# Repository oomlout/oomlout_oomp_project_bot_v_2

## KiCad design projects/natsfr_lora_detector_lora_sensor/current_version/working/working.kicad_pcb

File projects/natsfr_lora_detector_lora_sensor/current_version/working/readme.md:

# lora_detector
 
## summary 
* id: natsfr_lora_detector_lora_sensor
* user: natsfr
* name: lora_detector
* board: lora_sensor
* repo: https://github.com/natsfr/Lora_detector
* src_file_repo_kicad_pcb: sensor_board/lora_sensor/lora_sensor.kicad_pcb
* src_file_repo_kicad_pcb_link: https://github.com/natsfr/Lora_detector/tree/master/sensor_board/lora_sensor/lora_sensor.kicad_pcb
* src_file_repo_kicad_sch: sensor_board/lora_sensor/lora_sensor.kicad_sch
* src_file_repo_kicad_sch_link: https://github.com/natsfr/Lora_detector/tree/master/sensor_board/lora_sensor/lora_sensor.kicad_sch

* src_file_repo_sch: 
* src_file_repo_sch_link: https://github.com/natsfr/Lora_detector/tree/master/
* full details link: https://github.com/oomlout/oomlout_oomp_project_bot_v_2/tree/main/projects/natsfr_lora_detector_lora_sensor/current_version/working

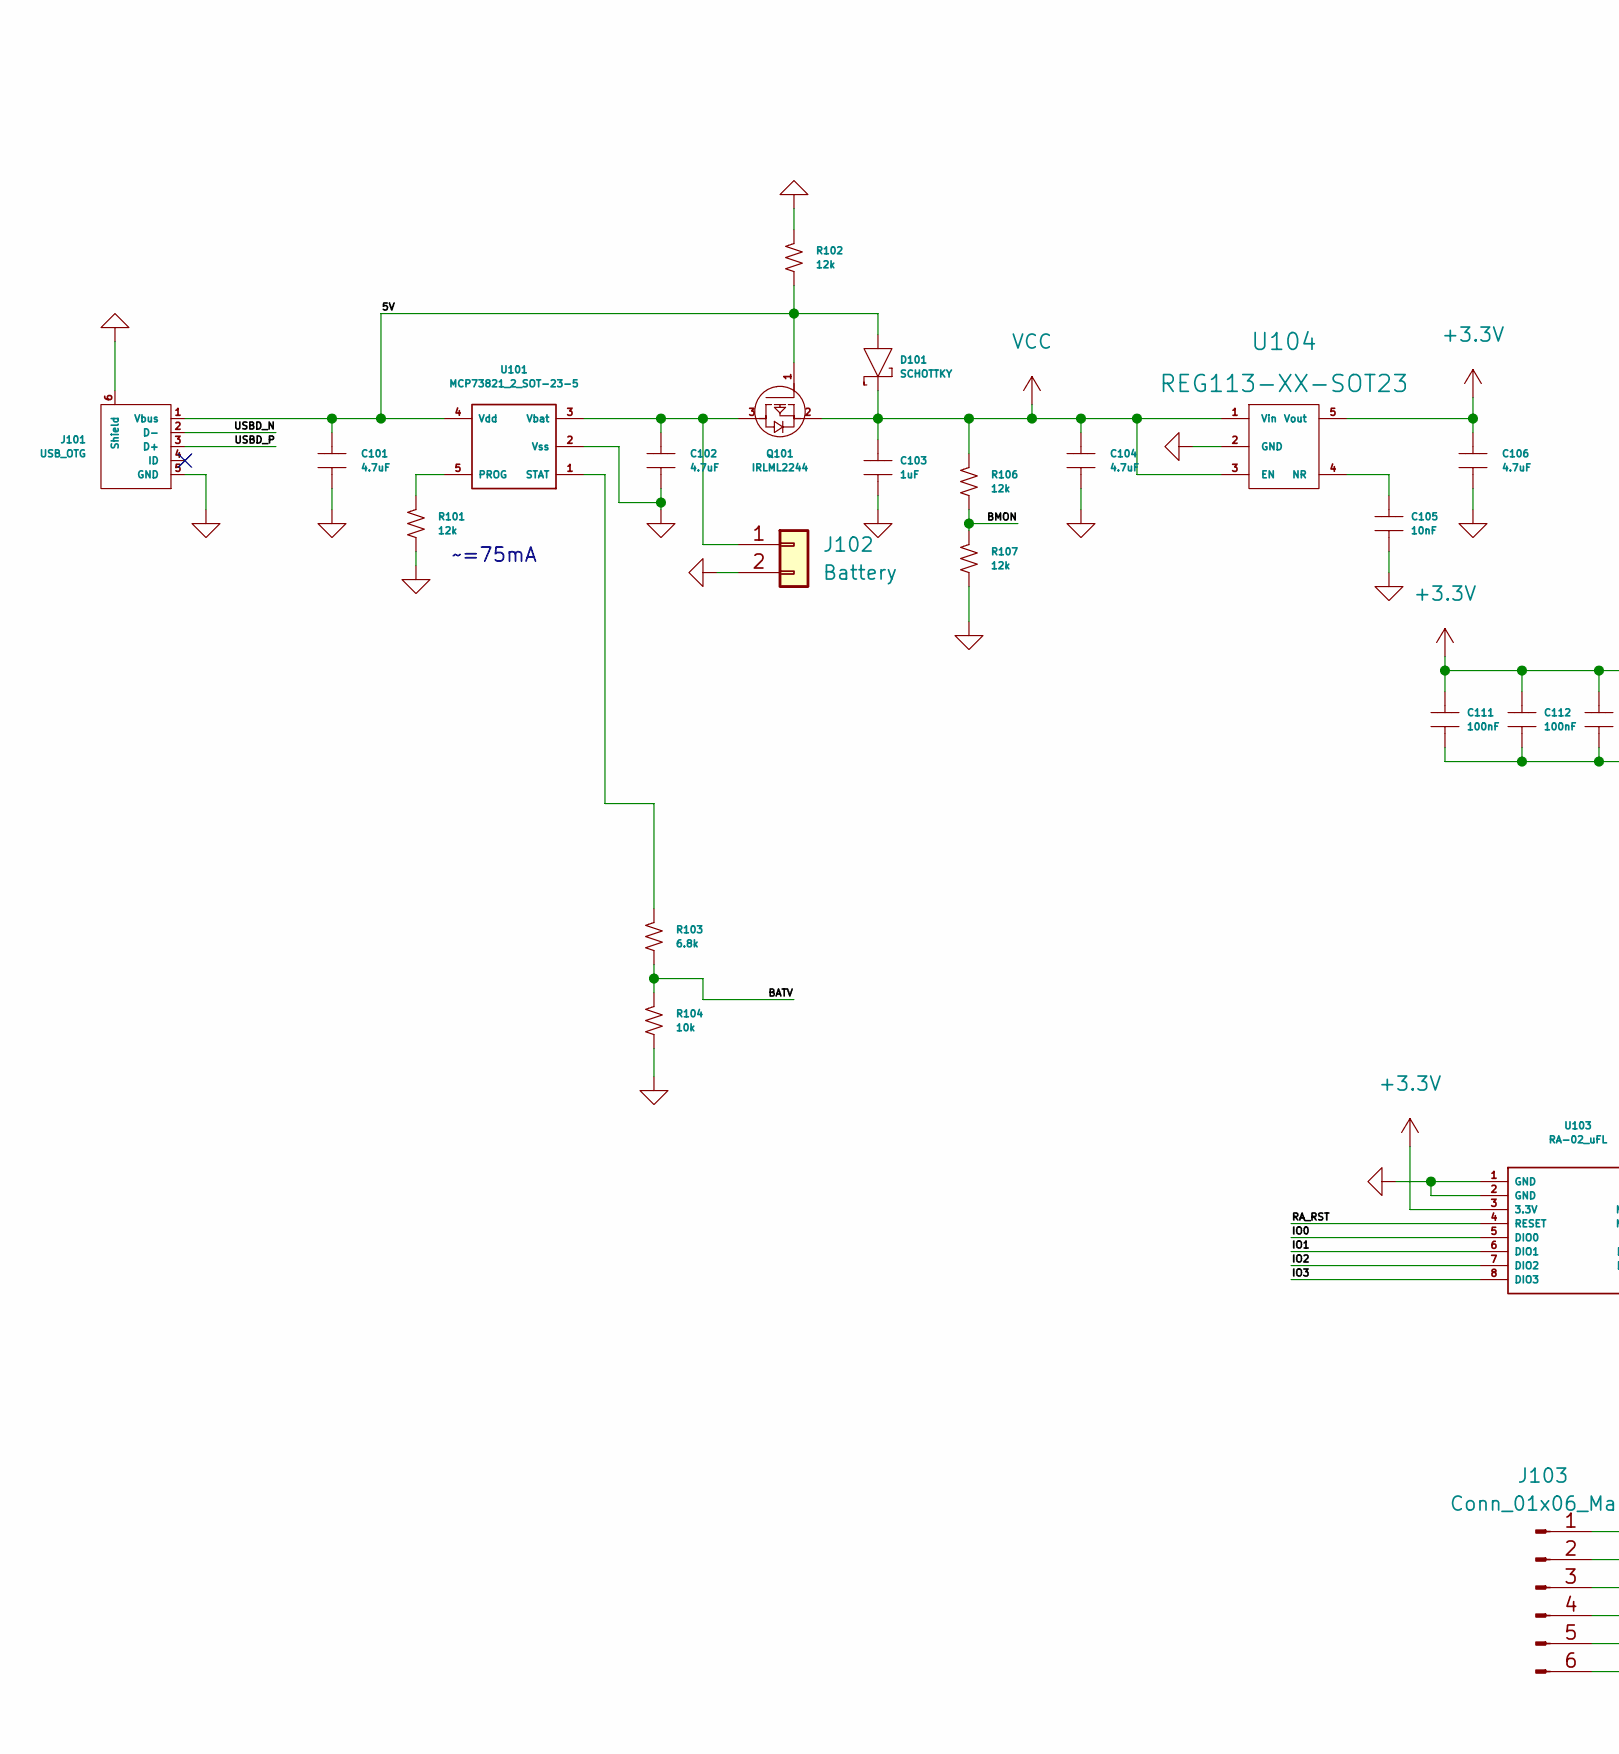
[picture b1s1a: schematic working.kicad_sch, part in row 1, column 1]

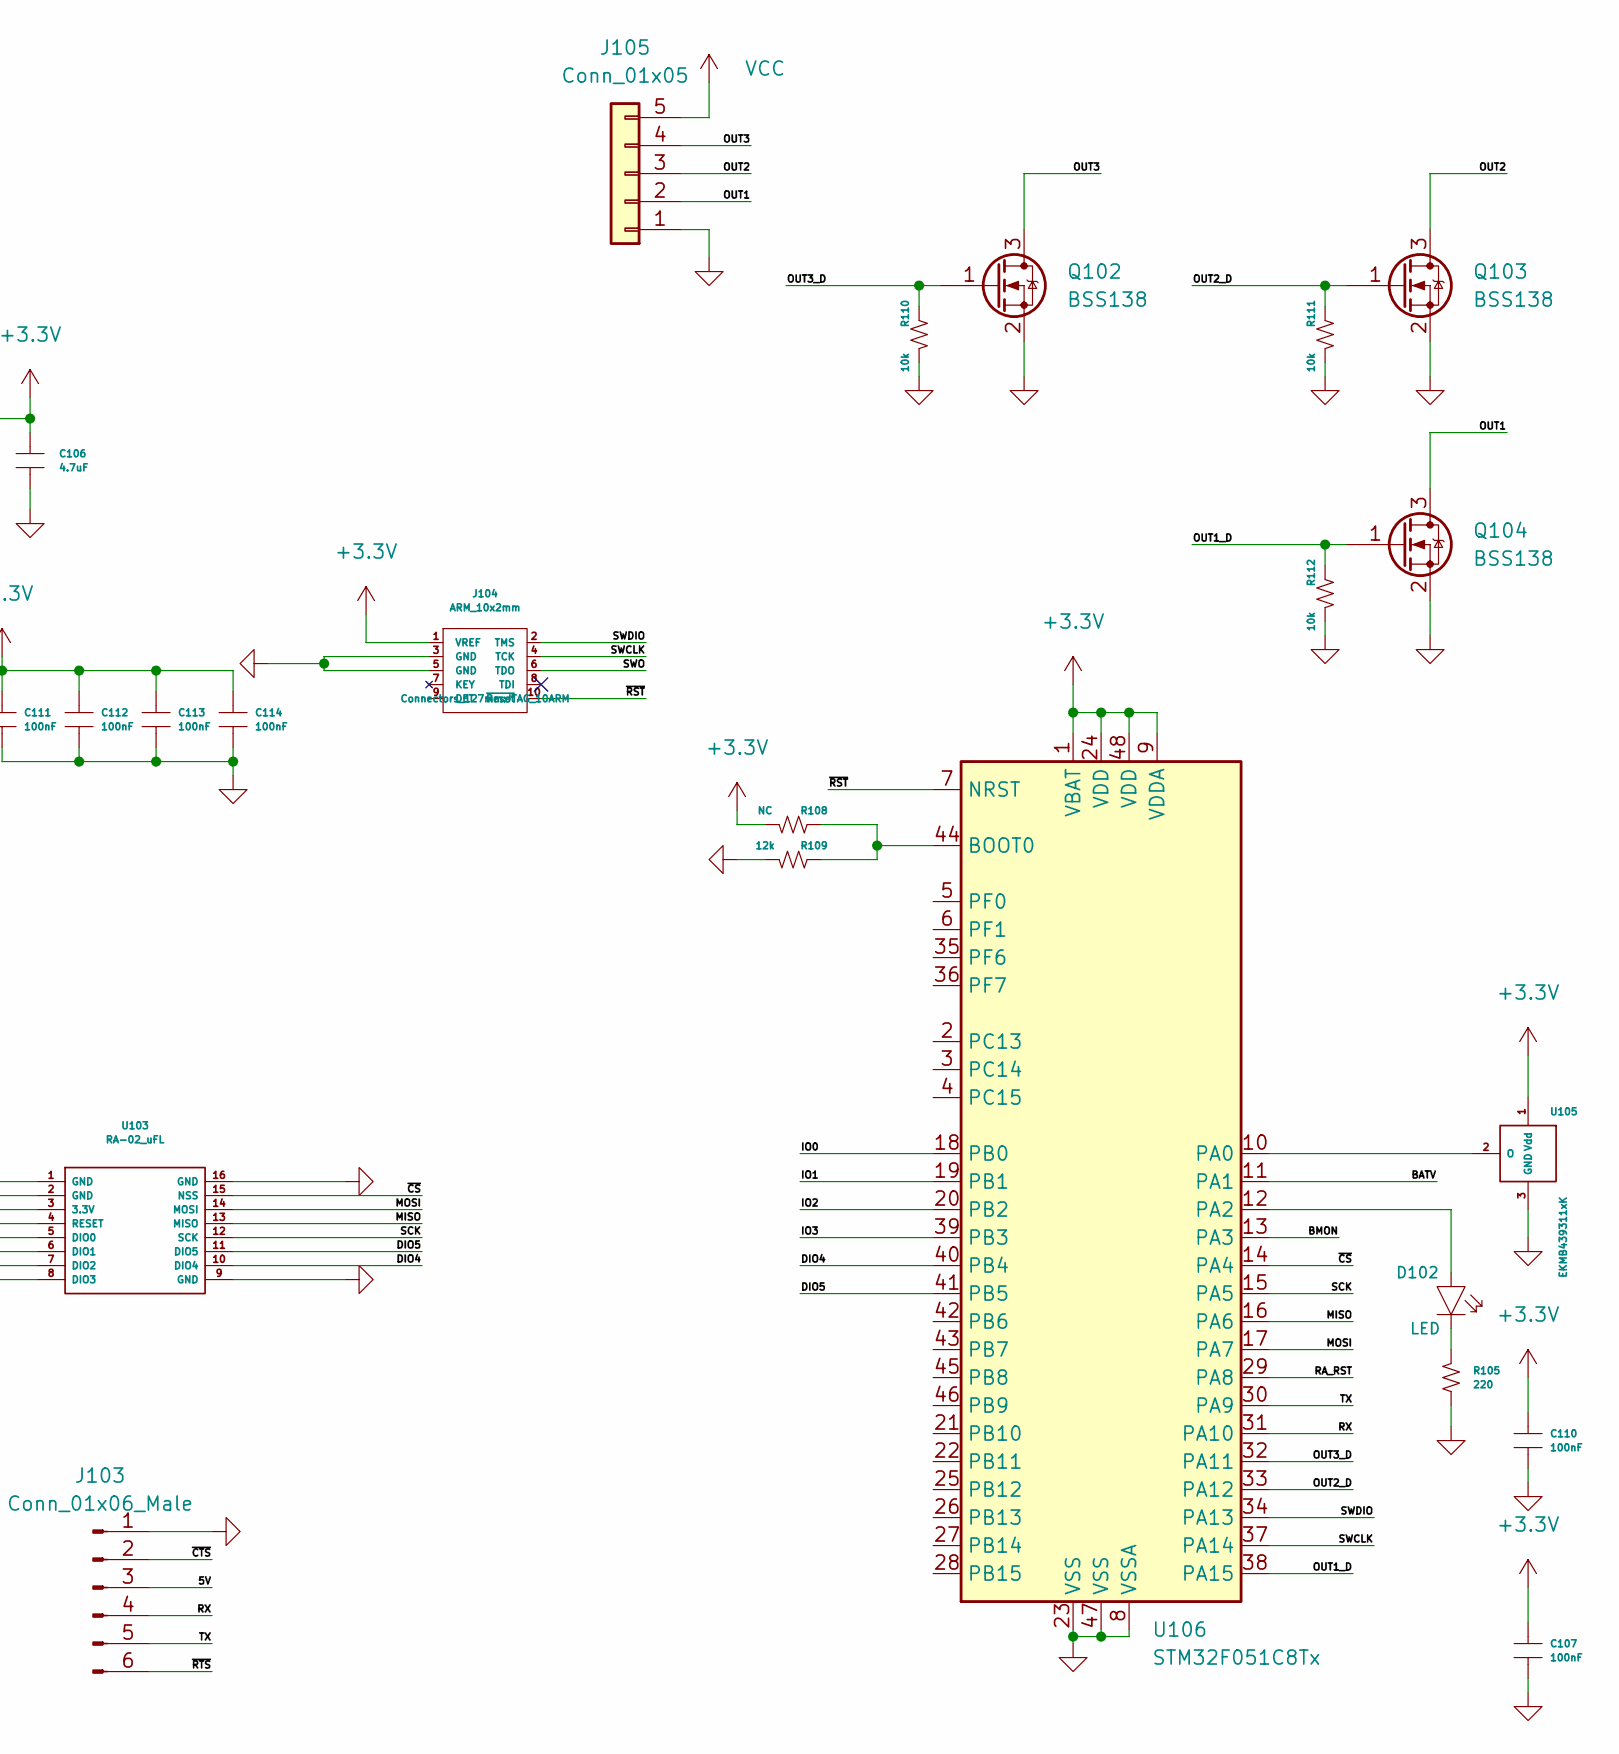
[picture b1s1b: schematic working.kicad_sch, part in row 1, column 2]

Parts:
C101, C102, C104, C106: 4.7uF; SM0805
C103: 1uF; SM0603
C105: 10nF; SM0603
C107, C110, C111, C112, C113, C114: 100nF; SM0603
D101: SCHOTTKY; SOD-123
D102: LED; LED-0805
J101: USB_OTG; USB_Micro-B_Wuerth_629105150521_CircularHoles
J102: Battery; JST_XH_B2B-XH-A_1x02_P2.50mm_Vertical
J103: Conn_01x06_Male; pin_array_6x1
J104: ARM_10x2mm; JTAG_10ARM
J105: Conn_01x05; JST_XH_B5B-XH-A_1x05_P2.50mm_Vertical
Q101: IRLML2244; SOT-23
Q102, Q103, Q104: BSS138; SOT-23
R101, R102, R106, R107, R109: 12k; SM0603
R103: 6.8k; SM0603
R104, R110, R111, R112: 10k; SM0603
R105: 220; SM0603
R108: NC; SM0603
U101: MCP73821_2_SOT-23-5; SOT23-5
U103: RA-02_uFL; RA-02_Lora
U104: REG113-XX-SOT23; SOT23-5
U105: EKMB439311xK
U106: STM32F051C8Tx; LQFP-48_7x7mm_P0.5mm

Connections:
+3V3: C106.2, C107.2, C110.2, C111.2, C112.2, C113.2, C114.2, J104.1 (VREF), R108.2, U103.3 (3.3V), U104.5 (Vout), U105.1 (Vdd), U106.1 (VBAT), U106.9 (VDDA), U106.24 (VDD), U106.48 (VDD)
/5V: C101.2, D101.A, J101.1 (Vbus), J103.3, Q101.1 (G), R102.1, U101.4 (Vdd)
/BATV: R103.1, R104.2, U106.11 (PA1)
/BMON: R106.1, R107.2, U106.13 (PA3)
/DIO4: U103.10 (DIO4), U106.40 (PB4)
/DIO5: U103.11 (DIO5), U106.41 (PB5)
/IO0: U103.5 (DIO0), U106.18 (PB0)
/IO1: U103.6 (DIO1), U106.19 (PB1)
/IO2: U103.7 (DIO2), U106.20 (PB2)
/IO3: U103.8 (DIO3), U106.39 (PB3)
/MISO: U103.13 (MISO), U106.16 (PA6)
/MOSI: U103.14 (MOSI), U106.17 (PA7)
/OUT1: J105.2, Q104.3 (D)
/OUT1_D: Q104.1 (G), R112.1, U106.38 (PA15)
/OUT2: J105.3, Q103.3 (D)
/OUT2_D: Q103.1 (G), R111.1, U106.33 (PA12)
/OUT3: J105.4, Q102.3 (D)
/OUT3_D: Q102.1 (G), R110.1, U106.32 (PA11)
/RA_RST: U103.4 (RESET), U106.29 (PA8)
/RX: J103.4, U106.31 (PA10)
/SCK: U103.12 (SCK), U106.15 (PA5)
/SWCLK: J104.4 (TCK), U106.37 (PA14)
/SWDIO: J104.2 (TMS), U106.34 (PA13)
/SWO: J104.6 (TDO)
/TX: J103.5, U106.30 (PA9)
/USBD_N: J101.2 (D-)
/USBD_P: J101.3 (D+)
/~CS: U103.15 (NSS), U106.14 (PA4)
/~CTS: J103.2
/~RST: J104.10 (~Reset), U106.7 (NRST)
/~RTS: J103.6
GND: C101.1, C102.1, C103.1, C104.1, C105.1, C106.1, C107.1, C110.1, C111.1, C112.1, C113.1, C114.1, J101.5 (GND), J101.6 (Shield), J102.2, J103.1, J104.3 (GND), J104.5 (GND), J105.1, Q102.2 (S), Q103.2 (S), Q104.2 (S), R101.1, R102.2, R104.1, R105.1, R107.1, R109.2, R110.2, R111.2, R112.2, U101.2 (Vss), U103.1 (GND), U103.2 (GND), U103.9 (GND), U103.16 (GND), U104.2 (GND), U105.3 (GND), U106.8 (VSSA), U106.23 (VSS), U106.47 (VSS)
unnamed: C102.2, J102.1, Q101.3 (D), U101.3 (Vbat)
unnamed: C105.2, U104.4 (NR)
unnamed: D102.K, R105.2
unnamed: R101.2, U101.5 (PROG)
unnamed: R103.2, U101.1 (STAT)
unnamed: U105.2 (O), U106.10 (PA0)
unnamed: D102.A, U106.12 (PA2)
unnamed: R108.1, R109.1, U106.44 (BOOT0)
VCC: C103.2, C104.2, D101.K, J105.5, Q101.2 (S), R106.2, U104.1 (Vin), U104.3 (EN)

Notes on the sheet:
~=75mA

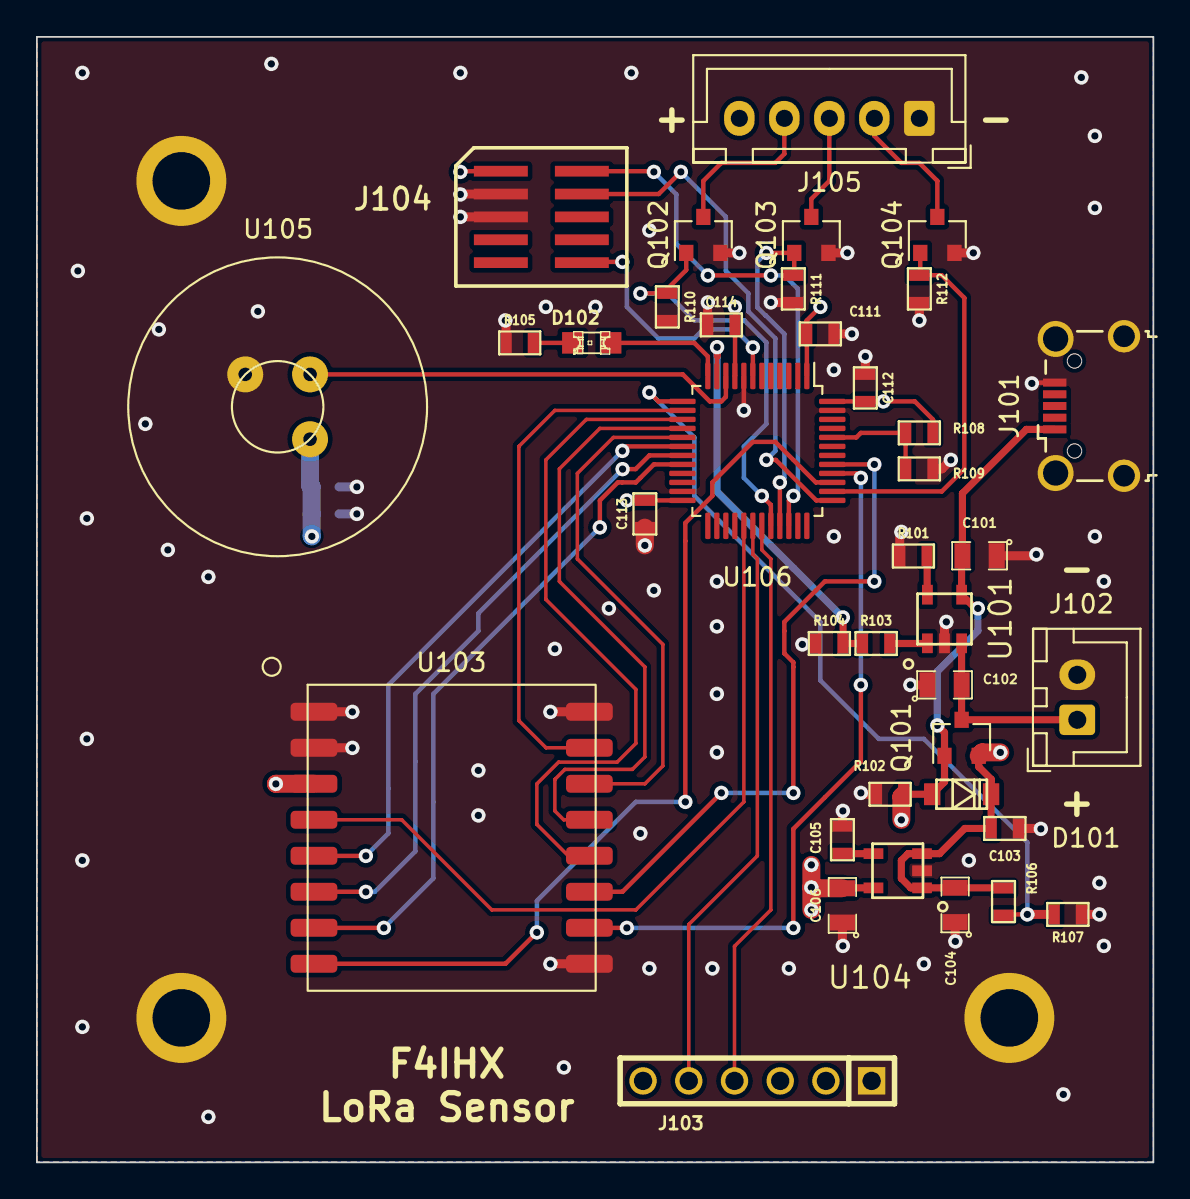
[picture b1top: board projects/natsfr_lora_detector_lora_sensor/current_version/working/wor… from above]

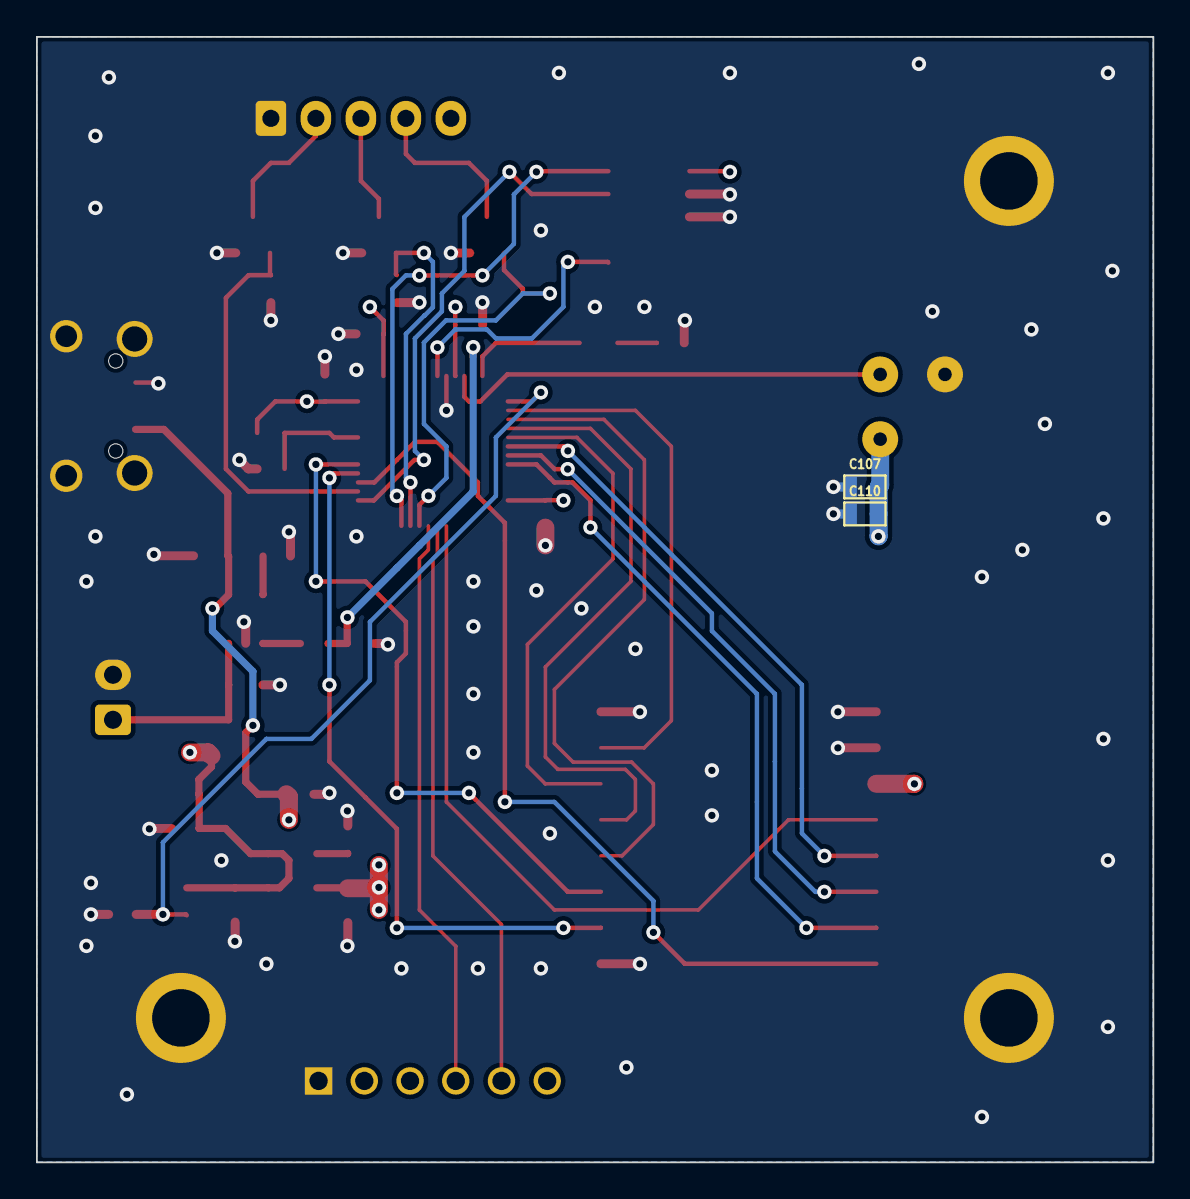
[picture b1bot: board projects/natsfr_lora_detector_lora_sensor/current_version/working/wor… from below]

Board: 4 copper layers, 62.0 x 62.5 mm, 40 parts (2 on the bottom side), 36 nets.

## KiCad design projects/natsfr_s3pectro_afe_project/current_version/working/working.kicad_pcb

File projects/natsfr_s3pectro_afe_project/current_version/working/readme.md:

# s3pectro
 
## summary 
* id: natsfr_s3pectro_afe_project
* user: natsfr
* name: s3pectro
* board: afe_project
* repo: https://github.com/natsfr/s3pectro
* src_file_repo_kicad_pcb: hardware/v0.1/30035_AFE/AFE_Project/AFE_Project.kicad_pcb
* src_file_repo_kicad_pcb_link: https://github.com/natsfr/s3pectro/tree/master/hardware/v0.1/30035_AFE/AFE_Project/AFE_Project.kicad_pcb

* src_file_repo_sch: hardware/v0.1/30035_AFE/AFE_Project/AFE_Project.sch
* src_file_repo_sch_link: https://github.com/natsfr/s3pectro/tree/master/hardware/v0.1/30035_AFE/AFE_Project/AFE_Project.sch
* full details link: https://github.com/oomlout/oomlout_oomp_project_bot_v_2/tree/main/projects/natsfr_s3pectro_afe_project/current_version/working

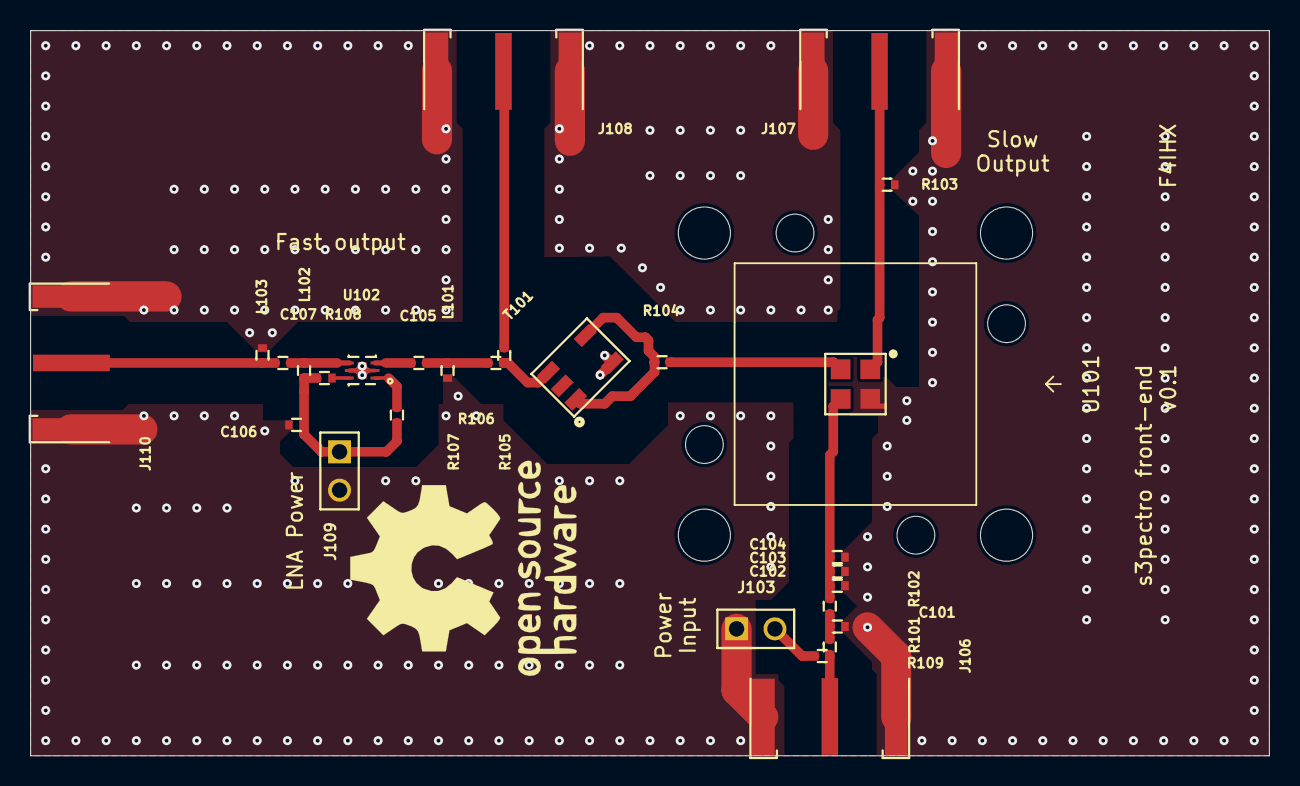
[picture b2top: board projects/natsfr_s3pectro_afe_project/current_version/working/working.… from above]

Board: 4 copper layers, 82.0 x 48.0 mm, 32 parts (0 on the bottom side), 17 nets.

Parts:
C101, C102, C103, C104: 10n; SM0402
C105, C107: 33p; SM0402
C106: 100nF; SM0402
J101, J102, J104, J105: Conn_01x01; 3.45MM_NOTPLATED
J103, J109: Conn_01x02; pin_array_2x1
J106, J107, J108, J110: SMA_142-0701-801; CINCH_142-0701-801
L101: 18nH; SM0402
L102: 33nH; SM0402
L103: NC; SM0402
R101, R102, R103: 49.9R; SM0402
R104, R105, R106, R109: 0R; SM0402
R107, R108: 75R; SM0402
T101: MABACT0059
U101: MICROFB-30035; MicroFC-30035-SMT
U102: GRF2133; DFN-6_EP_1.5x1.5_Pitch0.5mm

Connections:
/LEN: R107.2, U102.1
/LNA_POW: C106.1, J109.1, L102.2, R107.1, R108.2
/LNA_Vdd: R108.1, U102.6
/RF_slow_out: J107.1, R103.1, U101.1
/RFo: R104.1, U101.2
/RFo_0: C107.2, J110.1, L103.2
/RFo_1: C107.1, L102.1, U102.4
/RFo_2: C105.2, U102.3
/RFo_3: C105.1, L101.2, R106.2
/RFo_4: R105.1, R106.1, T101.3
/RFo_n: J108.1, R105.2
/RFo_t: R104.2, T101.1, T101.4
/RFpi: C102.2, C103.2, C104.2, R102.2, U101.3
/RFpi_0: J106.1, R101.1, R109.2
/RFpi_1: C101.2, R101.2, R102.1
/RFpi_p: J103.2, R109.1
GND: C101.1, C102.1, C103.1, C104.1, C106.2, J103.1, J106.2, J107.2, J108.2, J109.2, J110.2, L101.1, L103.1, R103.2, T101.5, U101.4, U102.2, U102.5, U102.7

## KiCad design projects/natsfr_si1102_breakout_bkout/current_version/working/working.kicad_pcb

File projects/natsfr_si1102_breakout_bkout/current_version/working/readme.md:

# si1102_breakout
 
## summary 
* id: natsfr_si1102_breakout_bkout
* user: natsfr
* name: si1102_breakout
* board: bkout
* repo: https://github.com/natsfr/SI1102_Breakout
* src_file_repo_kicad_pcb: bkout.kicad_pcb
* src_file_repo_kicad_pcb_link: https://github.com/natsfr/SI1102_Breakout/tree/master/bkout.kicad_pcb

* src_file_repo_sch: bkout.sch
* src_file_repo_sch_link: https://github.com/natsfr/SI1102_Breakout/tree/master/bkout.sch
* full details link: https://github.com/oomlout/oomlout_oomp_project_bot_v_2/tree/main/projects/natsfr_si1102_breakout_bkout/current_version/working

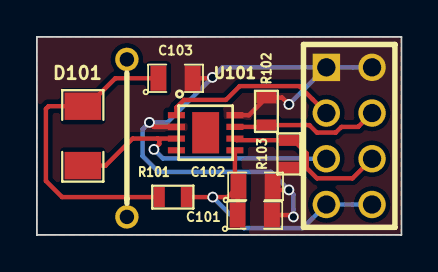
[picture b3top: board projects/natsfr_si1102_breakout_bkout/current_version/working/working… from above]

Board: 2 copper layers, 20.2 x 11.0 mm, 9 parts (0 on the bottom side), 7 nets.

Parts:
C101, C102, C103: CAP_0805; SM0805
D101: Led_Small; SM1206
P101: CONN_02X04; pin_array_4x2
R101, R102, R103: RES_0603; SM0603
U101: SI1102; ODFN-8_3x3

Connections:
/FR: P101.4, R102.1, U101.7
/PRX: P101.3, U101.1
/SREN: P101.6, R103.1, U101.6
/TXO: D101.2, P101.5, U101.3
GND: C101.2, C102.2, C103.2, P101.1, P101.2, R102.2, R103.2, U101.2, U101.8
unnamed: C103.1, D101.1, R101.2
VCC: C101.1, C102.1, P101.7, P101.8, R101.1, U101.5
